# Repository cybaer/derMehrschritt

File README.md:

# Eurorack Sequencer based on M-185

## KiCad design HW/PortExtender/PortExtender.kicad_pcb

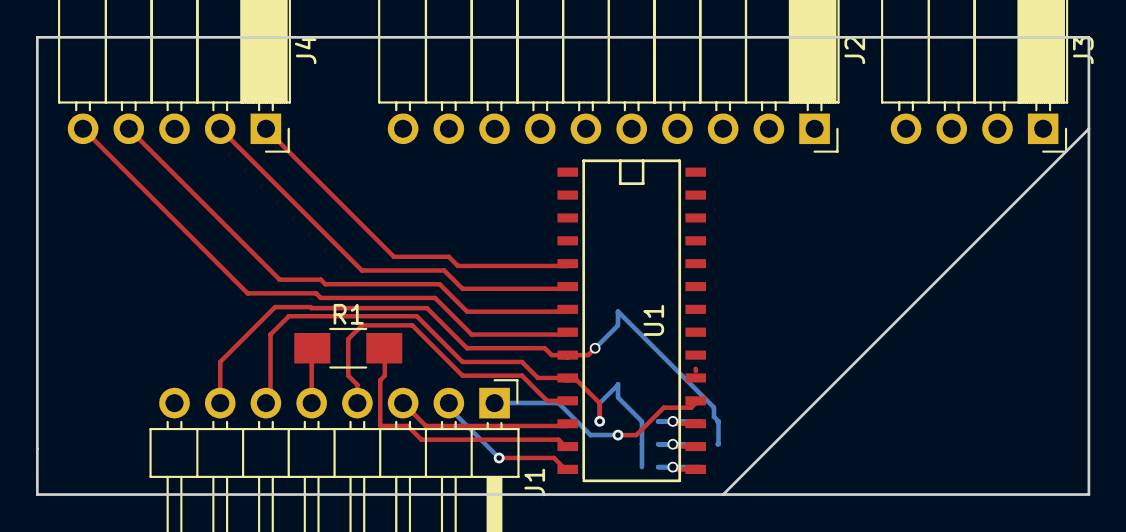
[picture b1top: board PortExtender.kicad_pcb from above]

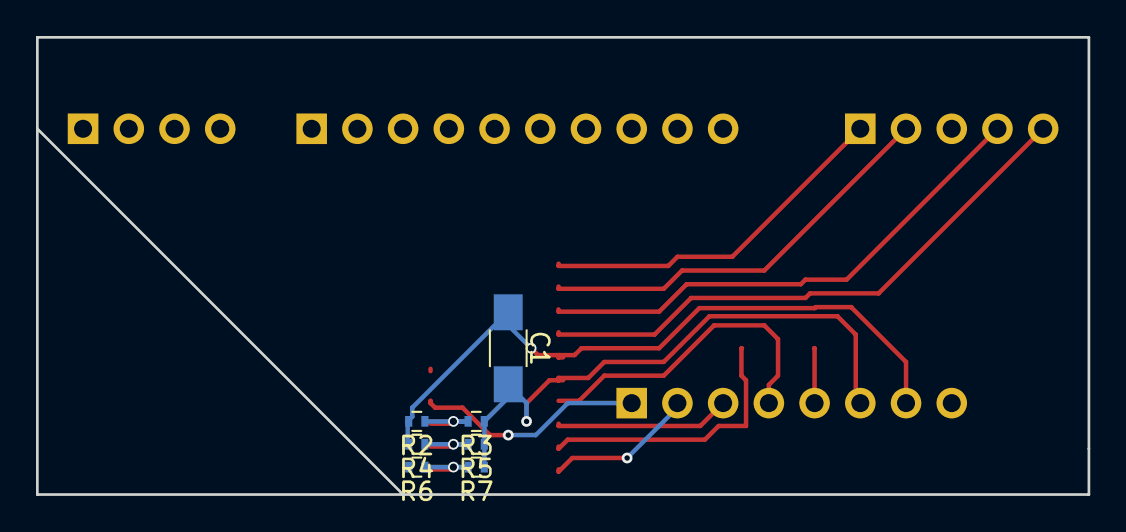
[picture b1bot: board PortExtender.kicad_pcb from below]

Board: 2 copper layers, 58.4 x 25.4 mm, 13 parts (7 on the bottom side), 15 nets.

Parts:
C1: C; C_1206_HandSoldering
J1: Conn_01x07_Male; Pin_Header_Angled_1x08_Pitch2.54mm
J2: Conn_01x10_Female; Socket_Strip_Angled_1x10_Pitch2.54mm
J3: Conn_01x04_Female; Socket_Strip_Angled_1x04_Pitch2.54mm
J4: Conn_01x05_Female; Socket_Strip_Angled_1x05_Pitch2.54mm
R1: R; R_1206_HandSoldering
R2, R3, R4, R5, R6, R7: R; R_0402
U1: MCP23S17; SOIC-28

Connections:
/B4: J4.1, U1.5
/B5: J4.2, U1.6
/B6: J4.4, U1.7
/B7: J4.5, U1.8
/CS: J1.4, U1.11
/Mi: J1.5, R1.1
/Mo: J1.2, U1.14
/Reset: J1.1, U1.18
/SCK: J1.3, U1.12
GND: C1.2, J1.6, R3.1, R5.1, R7.1, U1.10
unnamed: R1.2, U1.13
unnamed: R2.1, R3.2, U1.17
unnamed: R4.1, R5.2, U1.16
unnamed: R6.1, R7.2, U1.15
VCC: C1.1, J1.7, R2.2, R4.2, R6.2, U1.9

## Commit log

2015-09-02 readme
2015-09-15 Midi-Zeugs added
2015-09-17 Midi läuft DAC nur Code
2015-09-20 project files added
2015-09-25 DAC läuft
2015-10-25 Schnittstelle Midi --> DAC angepasst
2015-10-26 Bild verbessert
2015-11-15 neue Layouts
2015-11-15 Display-Treiber in Betrieb genommen Hardware läuft prinzipiell, Grundfunktionen
2015-11-16 SPI Umbau test für MCP23s17
2015-12-06 neue Bilder und Schaltungen aktualisiert
2015-12-06 neue Bilder
2015-12-12 LEDs und Taster funktionieren
2015-12-14 *project entfernt
2015-12-15 erste App: appHWTest
2016-01-03 neue Bilder für Midi-HW
2016-01-05 HW-Test erweitert Display update Page-weise
2016-01-06 Testimplementierung für Increment während Taste gedrückt
2016-01-06 HW-Test mit Anzeige
2016-02-03 Umstellung auf Submodules und make
2016-02-06 1. commit with Submodules and makefiles
2016-02-07 Base
2016-02-07 makefiles corrected
2016-02-08 AVRDUDE_LOCK = no
2016-02-08 avrlib makefile
2016-02-28 Test-Commit
2016-03-13 LockBits werden nicht mehr gesetzt
2016-04-25 Test erweitert auf dig. Ein- u. Ausgänge
2016-04-26 clock.h added
2016-04-27 clock erweitert
2016-04-28 erste clock Tests
2016-04-29 nochmehr clock Experimente
2016-05-01 appTriggerSequencer neu HW-Bilder update
2016-05-01 weiter HW-Bilder
2016-05-02 triggerSeq erweitert
2016-05-02 der TriggerSequencer tickt erste Gate-Signale werden entsprechend Muster erzeugt
2016-05-03 TriggerSeq mit Led-Ausgabe
2016-05-03 TriggerSeq mit Start/Stopp Reset BPM change
2016-05-04 TriggerSeq erweitert Anzeiger der gesetzten Steps im Edit-Mode
2016-05-04 Submodule avrlib updated
2016-05-08 LED-Anzeige erweitert
2016-05-09 Trigger Sequencer sendet Midi Noten Midi Daten Verarbeitung über Ringpuffer
2016-05-11 avril/ updated
2016-05-11 Ui: neue Funktion readSwitchMatrix() alle Taster der Matrix werden refreshed und der aktuelle Wert in m_Switches gespeichert
2016-05-11 Einstellen der Gate-Länger, erster Versuch
2016-05-13 Refactoring
2016-05-19 Performance Refactoring
2016-05-31 DAC, erster Wurf
2016-06-01 Skalierung und erter Versuch mit Hz/V
2016-06-02 refactoring scaler.h neu
2016-06-07 Refactoring Scaling-Tabelle für Hz/Volt
2016-06-08 Refactoring in scaler.h
2016-06-15 appHWTest als einfaches Midi2Cv
2016-06-15 new cv.h
2016-06-19 TrackLen und GateLen jetzt für jeden Track getrennt einstellbar nicht genutzte Steps werden rot angezeigt
2016-10-30 avrlib/ update
2018-05-22 new app for M185
2018-05-22 GFX-Library compilable
2018-05-22 some changes
2018-05-23 M185Sequencer.h added
2018-05-24 M185Sequenzer improved
2018-05-28 SingleStepper added
2018-05-31 SingleStepper continued
2018-06-08 some stepper stuff
2018-08-20 PortExtender PCB in KiCad
2018-08-23 M185Sequencer.cpp added
2018-09-23 Layout changed
2018-09-23 backup files removed
2018-09-30 commit submodules clock.h improved
2018-09-30 libs updated
2018-09-30 clock improved
2018-09-30 xlib removed
2018-09-30 lib already added
2018-09-30 Ada...
2018-10-01 test
